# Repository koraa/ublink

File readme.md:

# µBlink

PWM Control for high power leds

## Features

* ESP32 CPU
* Access console via USB
* External antenna support
* High Voltage Relais to turn 

## Copying

Copyright 2018-2019 by Karolin Varner.

Hardware is licensed under CERN Open Hardware Licence v1.2.
Software is licensed under MIT license.

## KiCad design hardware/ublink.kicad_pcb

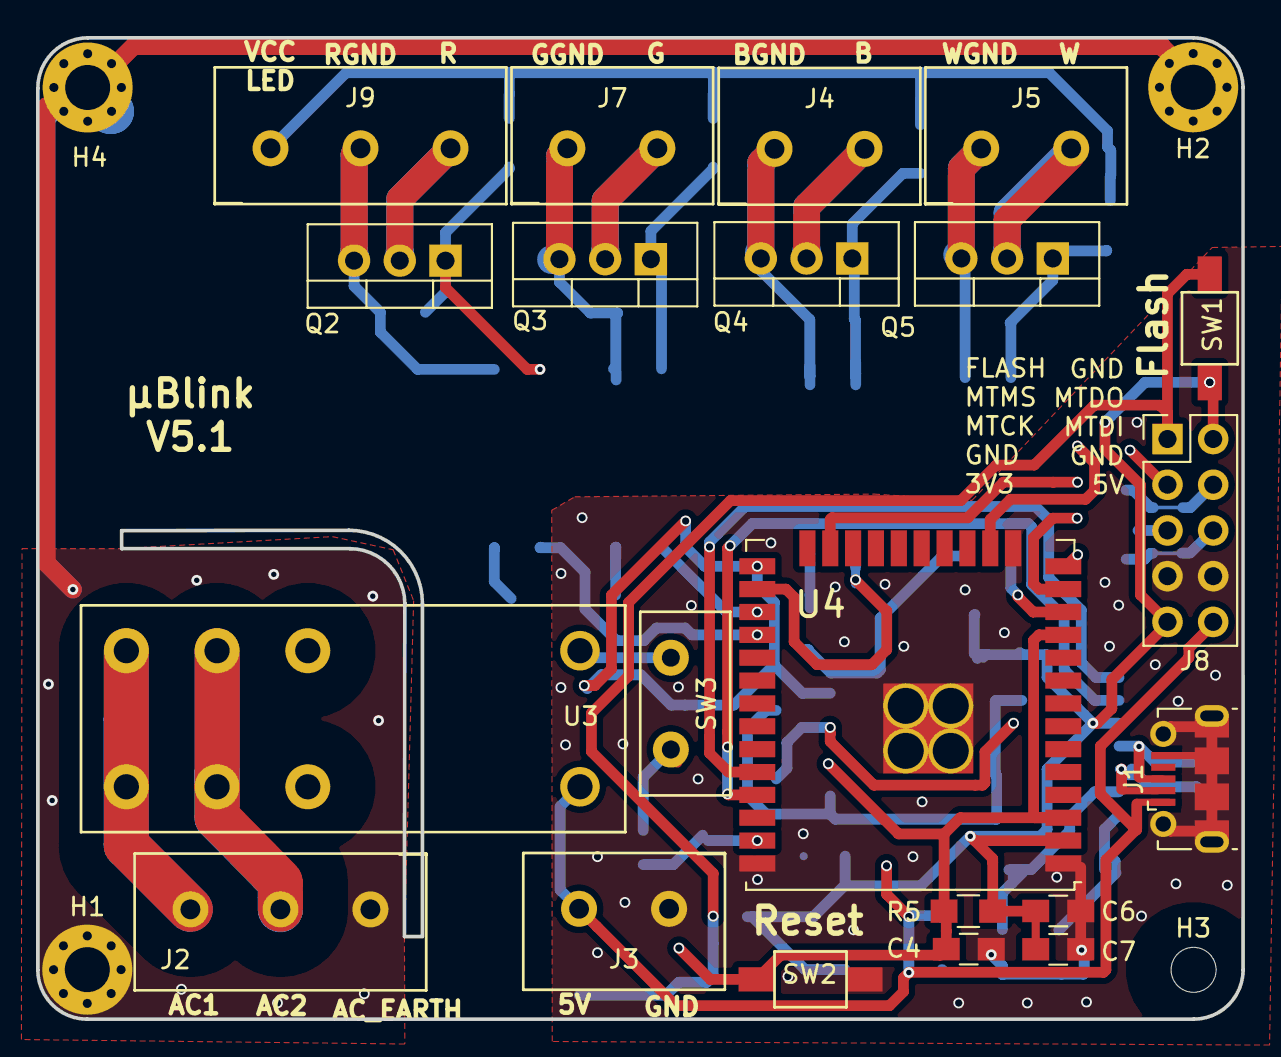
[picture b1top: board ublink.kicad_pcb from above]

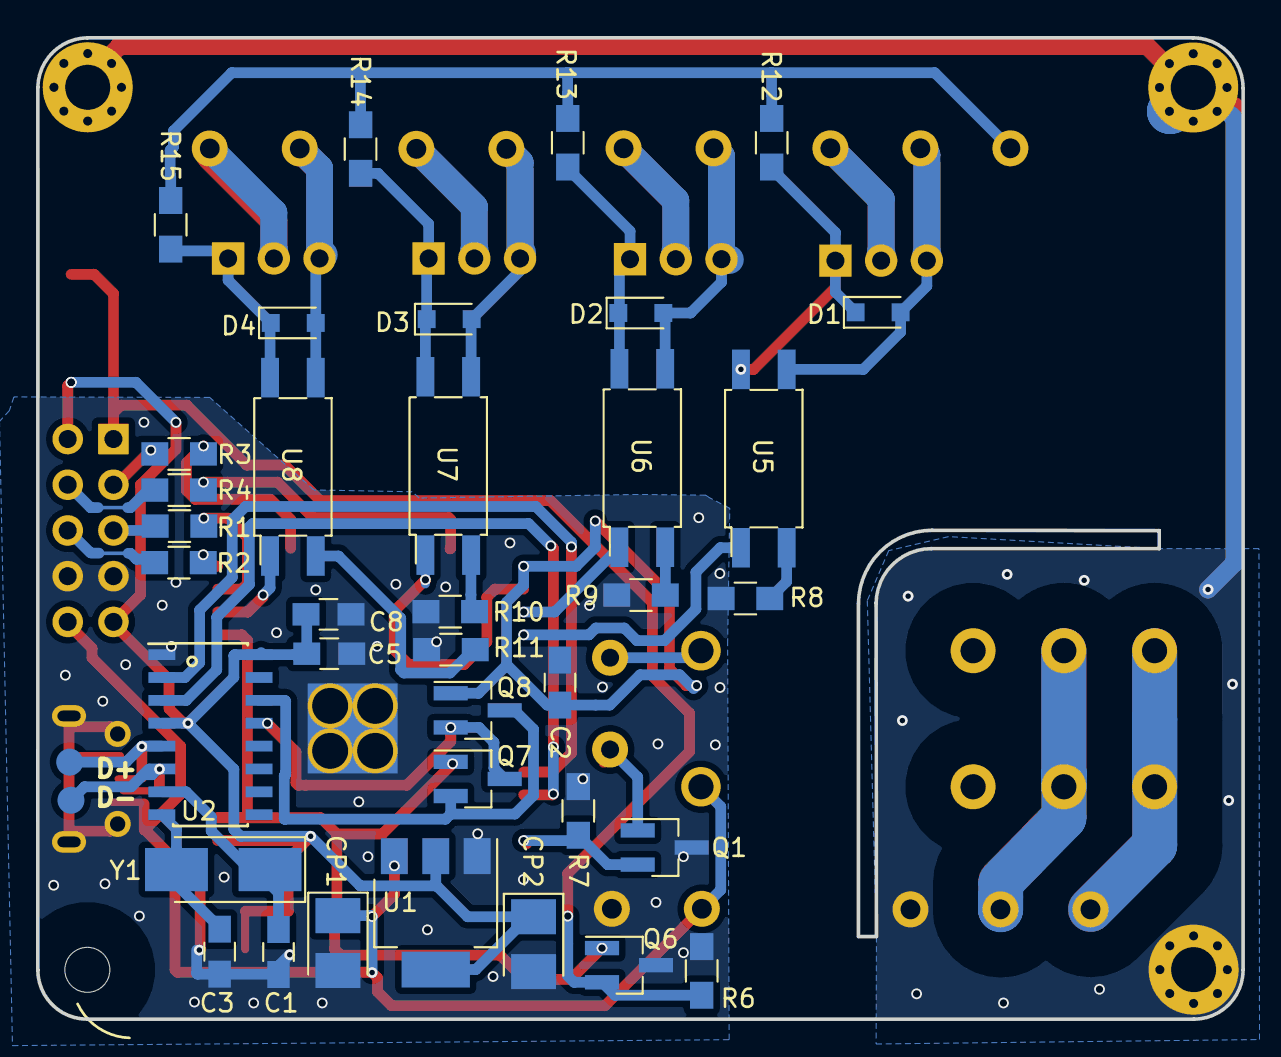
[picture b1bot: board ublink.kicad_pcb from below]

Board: 2 copper layers, 67.0 x 54.5 mm, 63 parts (38 on the bottom side), 49 nets.

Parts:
10u1: C8; C_0805_HandSoldering
10u2: C7; C_0805_HandSoldering
100u1: CP1; CP_Tantalum_Case-B_EIA-3528-21_Reflow
100u2: CP2; CP_Tantalum_Case-B_EIA-3528-21_Reflow
C1, C3: 22p; C_0805_HandSoldering
C2: 2u; C_0805_HandSoldering
C4: 0.1u; C_0805_HandSoldering
C5, C6: 100n; C_0805_HandSoldering
D1, D2, D3, D4: 18V; D_SOD-323_HandSoldering
H1, H2, H4: MountingHole; MountingHole_2.5mm_Pad_Via
H3: MountingHole; MountingHole_2.5mm
J1: USB_B_Micro; USB_Micro-B_Molex-105017-0001
J2: AC1; KF301-5.0-3P
J3: 5V Trafo; KF301-5.0-2P
J4, J5, J7: Screw_Terminal_01x02; KF301-5.0-2P
J8: Pin Header; Pin_Header_Straight_2x05_Pitch2.54mm
J9: Screw_Terminal_01x02; KF301-5.0-3P
Q1, Q6, Q7, Q8: STN3NF06L; SOT-23_Handsoldering
Q2, Q3, Q4, Q5: RU6099; TO-220-3_Vertical
R1, R2, R3, R4, R8, R9, R10, R11: 100; R_0805_HandSoldering
R5, R6, R7: 10k; R_0805_HandSoldering
R12, R13, R14, R15: 20k; R_0805_HandSoldering
SW1, SW2: SW_Push; pushbutton_2
SW3: JUC-31F
TP1, TP2: TestPoint; Measurement_Point_Round-SMD-Pad_Small
U1: 3.3V3 Regul; lm-1117
U2: CH340G; CH403G
U3: HF115F_005-1ZS3
U4: ESP32-WROOM-32U
U5, U6, U7, U8: EL817S
Y1: 12Mhz; Crystal_SMD_5032-2pin_5.0x3.2mm_HandSoldering

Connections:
3V3: 10u1.1, 10u2.1, 100u2.1, C5.1, C6.1, J8.2, J8.9, R5.1, SW1.2, U1.2, U2.4, U2.16, U4.2
5V: 100u1.1, J1.1, J3.2, J8.10, U1.3, U3.1
/B_GATE: D3.1, Q4.1, R14.2, U7.4
/B_GND: D3.2, J4.1, Q4.3, U7.3
/B_LED: J4.2, Q4.2
/G_GATE: D2.1, Q3.1, R13.2, U6.4
/G_GND: D2.2, J7.1, Q3.3, U6.3
/G_LED: J7.2, Q3.2
/LED_VCC: J9.1, R12.1, R13.1, R14.1, R15.1
/R_GATE: D1.1, Q2.1, R12.2, U5.4
/R_GND: D1.2, J9.2, Q2.3, U5.3
/R_LED: J9.3, Q2.2
/USB_D+: J1.3, TP2.1, U2.5
/USB_D-: J1.2, TP1.1, U2.6
/W_GATE: D4.1, Q5.1, R15.2, U8.4
/W_GND: D4.2, J5.1, Q5.3, U8.3
/W_LED: J5.2, Q5.2
/XI: C1.1, U2.7, Y1.1
AC1: J2.2, U3.5, U3.6
AC2: J2.3, U3.7, U3.8
AC_SAFE: H1.1, H2.1, H4.1, J2.1
B_CTRL: U4.26, U7.1
DTR: Q7.3, Q8.2, U2.13
EN: C4.1, Q6.1, Q7.1, R5.2, SW2.2, U4.3, U4.11
FLASH: C2.1, Q8.1, U4.25
FLASH_BTN: J8.1, Q6.2, R6.1, SW1.1
GND: 10u1.2, 10u2.2, 100u1.2, 100u2.2, C1.2, C2.2, C3.2, C4.2, C5.2, C6.2, J1.5, J1.6, J3.1, J8.7, J8.8, Q1.3, Q6.3, R6.2, R7.2, R8.1, R9.1, R10.1, R11.1, SW2.1, U1.1, U2.1, U4.1, U4.15, U4.38, U4.39
G_CTRL: U4.27, U6.1
MTCK: R3.1, U4.16
MTDI: R2.2, U4.14
MTDO: R4.2, U4.23
MTMS: R1.1, U4.13
unnamed: C3.1, U2.8, Y1.2
unnamed: J8.3, R3.2
unnamed: J8.4, R4.1
unnamed: J8.5, R1.2
unnamed: J8.6, R2.1
unnamed: Q1.1, SW3.1
unnamed: R8.2, U5.2
unnamed: R9.2, U6.2
unnamed: R10.2, U7.2
unnamed: R11.2, U8.2
unnamed: SW3.2, U3.2
RELAIS_CTRL: Q1.2, R7.1, U4.37
RTS: Q7.2, Q8.3, U2.14
RX: U2.3, U4.35
R_CTRL: U4.28, U5.1
TX: U2.2, U4.34
W_CTRL: U4.12, U8.1

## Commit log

2019-06-26 initial
2019-07-23 Add dummy version of firmware
2019-07-25 Fix layout errors
2019-07-31 Initial firmware
2019-08-02 Animate a single led
2019-08-03 v5 PCB: Flash button nau auto resets
    Flash button exposed via pin headers; no more UART
    via pin headers.
    Lights are on pins that can actually be used.
2019-08-03 Release on GH
2019-08-04 Basic console output
2019-08-04 Hardware v5.1: Reset when DTR is high
    This allows esptool.py to reset the µC and boot into
    uart downloader mode without the user having to press
    a button.
2019-08-05 Reduce number of components built
2019-08-19 stash
